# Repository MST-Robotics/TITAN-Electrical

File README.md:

# TITAN-Electrical

This repository holds the electrical schematics and board layouts for
the ROV (TITAN II) being built by the Missouri University of Science and
Technology Underwater Robotics Design Team.

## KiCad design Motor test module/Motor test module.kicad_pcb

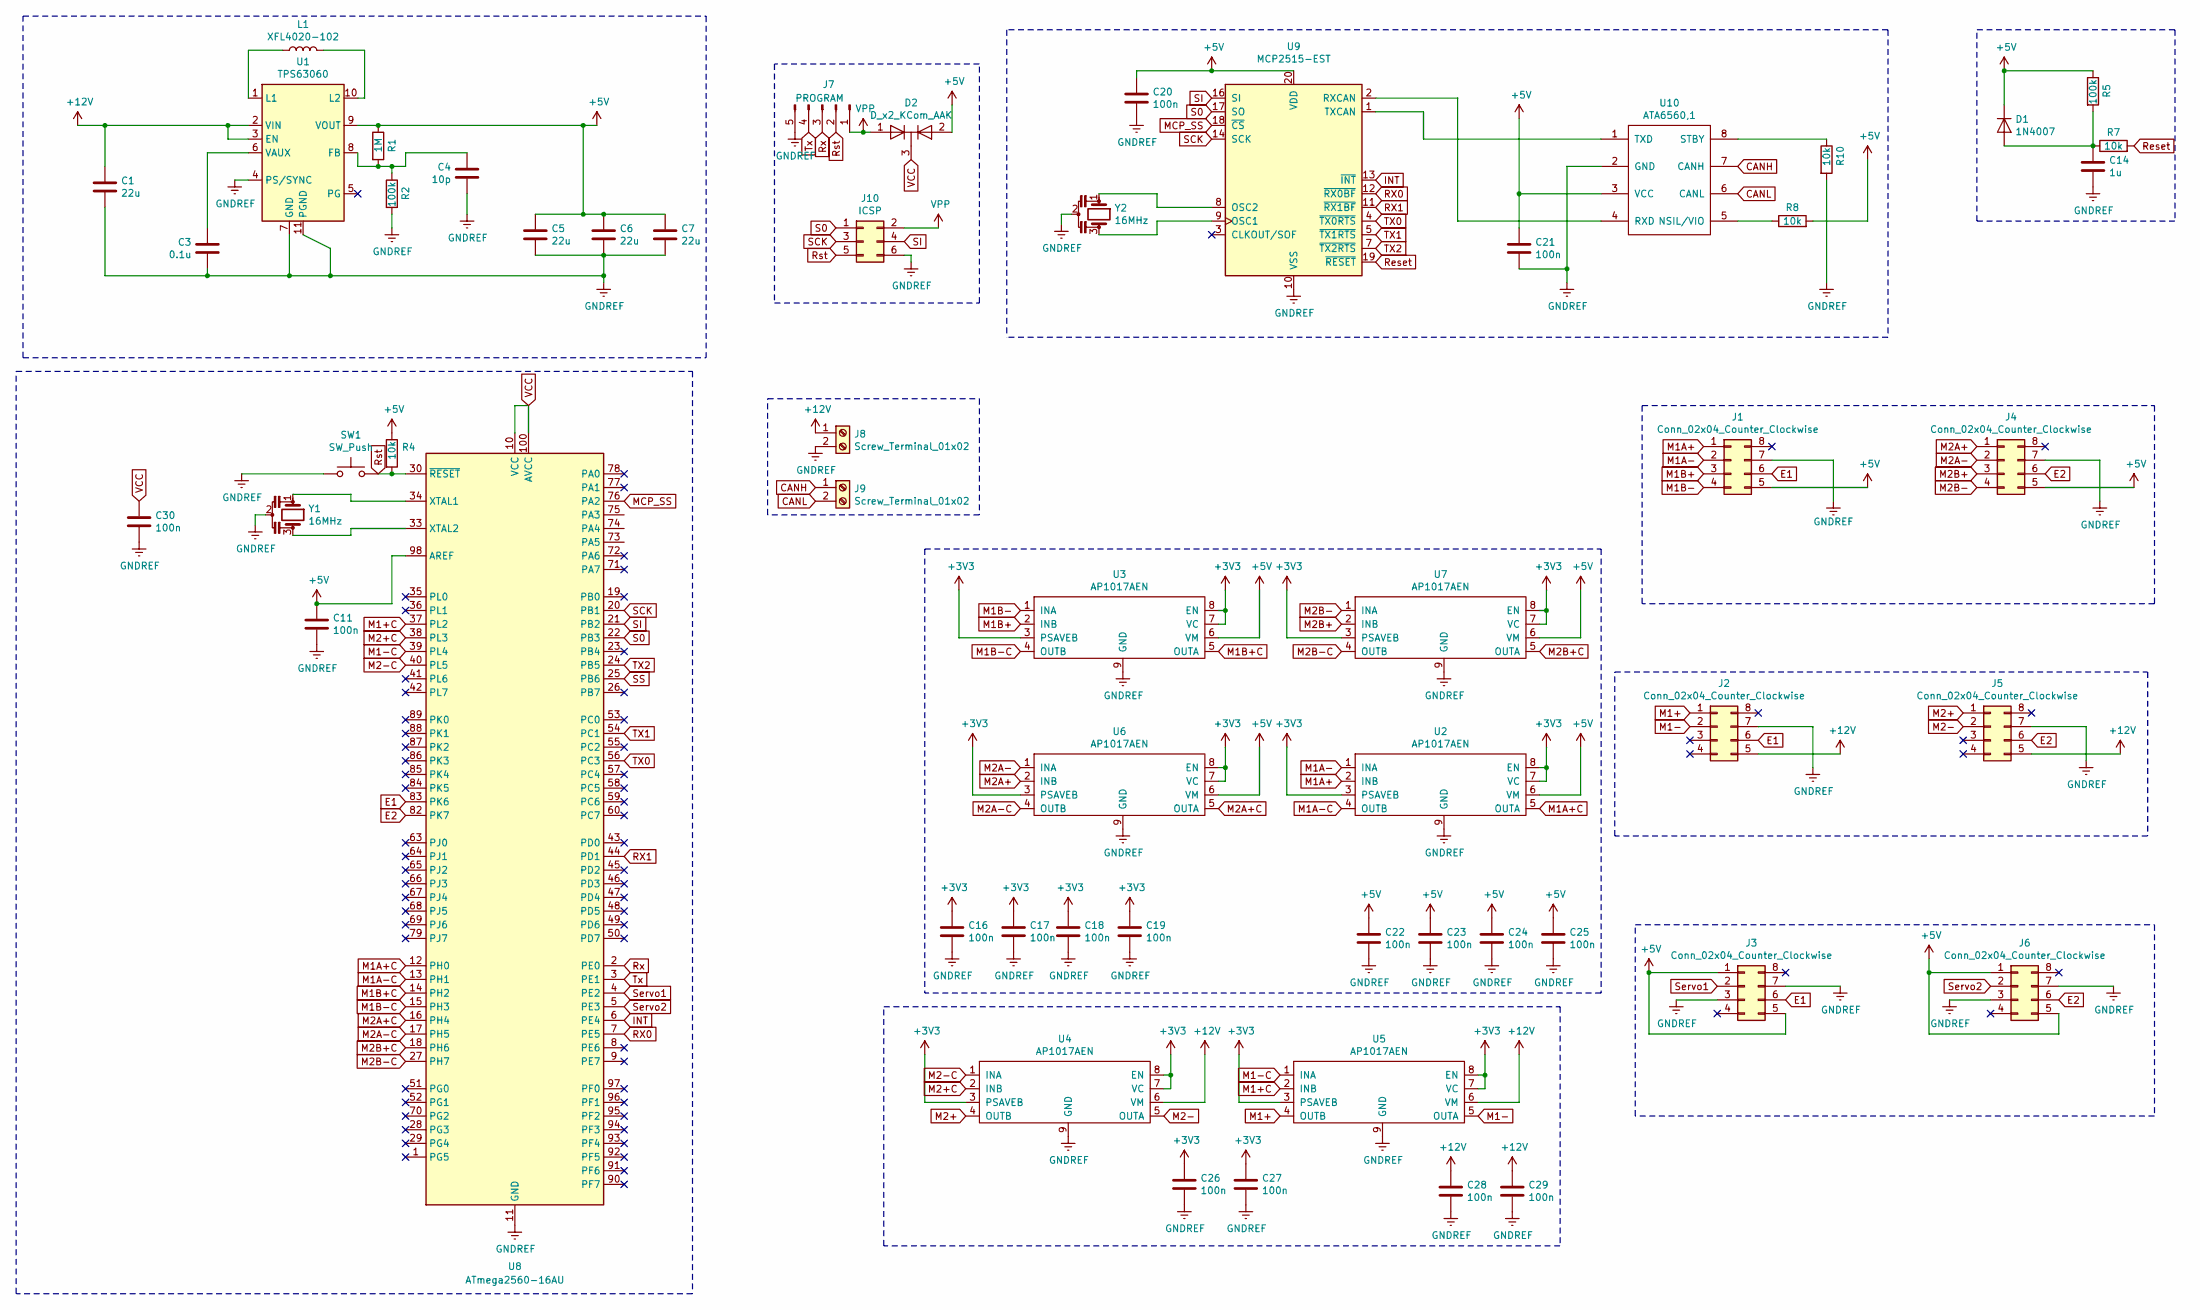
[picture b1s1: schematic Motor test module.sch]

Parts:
C1, C5, C6, C7: 22u; C_0805_2012Metric
C3: 0.1u; C_0603_1608Metric
C4: 10p; C_0603_1608Metric
C11, C16, C17, C18, C19, C20, C21, C22, C23, C24, C25, C26, C27, C28, C29, C30: 100n; C_0603_1608Metric
C14: 1u; C_0603_1608Metric
D1: 1N4007; D_DO-41_SOD81_P2.54mm_Vertical_AnodeUp
D2: D_x2_KCom_AAK; SOT-23
J1, J2, J3, J4, J5, J6: Conn_02x04_Counter_Clockwise; PinHeader_2x04_P2.54mm_Vertical
J7: PROGRAM; PinHeader_1x05_P2.54mm_Vertical
J8, J9: Screw_Terminal_01x02; TerminalBlock_bornier-2_P5.08mm
J10: ICSP; PinHeader_2x03_P2.54mm_Vertical
L1: XFL4020-102; L_0603_1608Metric
R1: 1M; R_0603_1608Metric
R2, R5: 100k; R_0603_1608Metric
R4, R7, R8, R10: 10k; R_0603_1608Metric
SW1: SW_Push; SW_PUSH_6mm
U1: TPS63060; Texas_S-PWSON-N10_ThermalVias
U2, U3, U4, U5, U6, U7: AP1017AEN; WSON-8-1EP_2x2mm_P0.5mm_EP0.9x1.6mm
U8: ATmega2560-16AU; TQFP-100_14x14mm_P0.5mm
U9: MCP2515-EST; TSSOP-20_4.4x6.5mm_P0.65mm
U10: ATA6560,1; SO-8_5.3x6.2mm_P1.27mm
Y1, Y2: 16MHz; Resonator_SMD_muRata_CSTxExxV-3Pin_3.0x1.1mm

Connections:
+3V3: C16.1, C17.1, C18.1, C19.1, C26.1, C27.1, U2.3 (PSAVEB), U2.7 (VC), U2.8 (EN), U3.3 (PSAVEB), U3.7 (VC), U3.8 (EN), U4.3 (PSAVEB), U4.7 (VC), U4.8 (EN), U5.3 (PSAVEB), U5.7 (VC), U5.8 (EN), U6.3 (PSAVEB), U6.7 (VC), U6.8 (EN), U7.3 (PSAVEB), U7.7 (VC), U7.8 (EN)
+5V: C5.1, C6.1, C7.1, C11.1, C20.1, C21.1, C22.1, C23.1, C24.1, C25.1, D1.1 (K), D2.2 (A), J1.5, J3.1, J3.5, J4.5, J6.1, J6.5, R1.1, R4.1, R5.1, R8.2, U1.9 (VOUT), U2.6 (VM), U3.6 (VM), U6.6 (VM), U7.6 (VM), U8.98 (AREF), U9.20 (VDD), U10.3 (VCC)
+12V: C1.1, C28.1, C29.1, J2.5, J5.5, J8.1, U1.2 (VIN), U1.3 (EN), U4.6 (VM), U5.6 (VM)
CANH: J9.1, U10.7 (CANH)
CANL: J9.2, U10.6 (CANL)
E1: J1.6, J2.6, J3.6, U8.83 (PK6)
E2: J4.6, J5.6, J6.6, U8.82 (PK7)
GNDREF: C1.2, C3.1, C4.1, C5.2, C6.2, C7.2, C11.2, C14.2, C16.2, C17.2, C18.2, C19.2, C20.2, C21.2, C22.2, C23.2, C24.2, C25.2, C26.2, C27.2, C28.2, C29.2, C30.2, J1.7, J2.7, J3.3, J3.7, J4.7, J5.7, J6.3, J6.7, J7.5, J8.2, J10.6, R2.2, R10.2, SW1.1, U1.4 (PS/SYNC), U1.7 (GND), U1.11 (PGND), U2.9 (GND), U3.9 (GND), U4.9 (GND), U5.9 (GND), U6.9 (GND), U7.9 (GND), U8.11 (GND), U8.32 (GND), U8.62 (GND), U8.81 (GND), U8.99 (GND), U9.10 (VSS), U10.2 (GND), Y1.2, Y2.2
INT: U8.6 (PE4), U9.13 (~INT)
M1+: J2.1, U5.4 (OUTB)
M1+C: U5.2 (INB), U8.37 (PL2)
M1-: J2.2, U5.5 (OUTA)
M1-C: U5.1 (INA), U8.39 (PL4)
M1A+: J1.1, U2.2 (INB)
M1A+C: U2.5 (OUTA), U8.12 (PH0)
M1A-: J1.2, U2.1 (INA)
M1A-C: U2.4 (OUTB), U8.13 (PH1)
M1B+: J1.3, U3.2 (INB)
M1B+C: U3.5 (OUTA), U8.14 (PH2)
M1B-: J1.4, U3.1 (INA)
M1B-C: U3.4 (OUTB), U8.15 (PH3)
M2+: J5.1, U4.4 (OUTB)
M2+C: U4.2 (INB), U8.38 (PL3)
M2-: J5.2, U4.5 (OUTA)
M2-C: U4.1 (INA), U8.40 (PL5)
M2A+: J4.1, U6.2 (INB)
M2A+C: U6.5 (OUTA), U8.16 (PH4)
M2A-: J4.2, U6.1 (INA)
M2A-C: U6.4 (OUTB), U8.17 (PH5)
M2B+: J4.3, U7.2 (INB)
M2B+C: U7.5 (OUTA), U8.18 (PH6)
M2B-: J4.4, U7.1 (INA)
M2B-C: U7.4 (OUTB), U8.27 (PH7)
MCP_SS: U8.76 (PA2), U9.18 (~CS)
unnamed: C3.2, U1.6 (VAUX)
unnamed: C4.2, R1.2, R2.1, U1.8 (FB)
unnamed: C14.1, D1.2 (A), R5.2, R7.1
unnamed: L1.1, U1.1 (L1)
unnamed: L1.2, U1.10 (L2)
unnamed: R8.1, U10.5 (NSIL/VIO)
unnamed: R10.1, U10.8 (STBY)
unnamed: U8.33 (XTAL2), Y1.3
unnamed: U8.34 (XTAL1), Y1.1
unnamed: U9.8 (OSC2), Y2.1
unnamed: U9.9 (OSC1), Y2.3
unnamed: U9.1 (TXCAN), U10.1 (TXD)
unnamed: U9.2 (RXCAN), U10.4 (RXD)
RX0: U8.7 (PE5), U9.12 (~RX0BF)
RX1: U8.44 (PD1), U9.11 (~RX1BF)
Reset: R7.2, U9.19 (~RESET)
Rst: J7.2, J10.5, R4.2, SW1.2, U8.30 (~RESET)
Rx: J7.3, U8.2 (PE0)
S0: J10.1, U8.22 (PB3), U9.17 (SO)
SCK: J10.3, U8.20 (PB1), U9.14 (SCK)
SI: J10.4, U8.21 (PB2), U9.16 (SI)
Servo1: J3.2, U8.4 (PE2)
Servo2: J6.2, U8.5 (PE3)
TX0: U8.56 (PC3), U9.4 (~TX0RTS)
TX1: U8.54 (PC1), U9.5 (~TX1RTS)
TX2: U8.24 (PB5), U9.7 (~TX2RTS)
Tx: J7.4, U8.3 (PE1)
VCC: C30.1, D2.3 (K), U8.10 (VCC), U8.31 (VCC), U8.61 (VCC), U8.80 (VCC), U8.100 (AVCC)
VPP: D2.1 (A), J7.1, J10.2

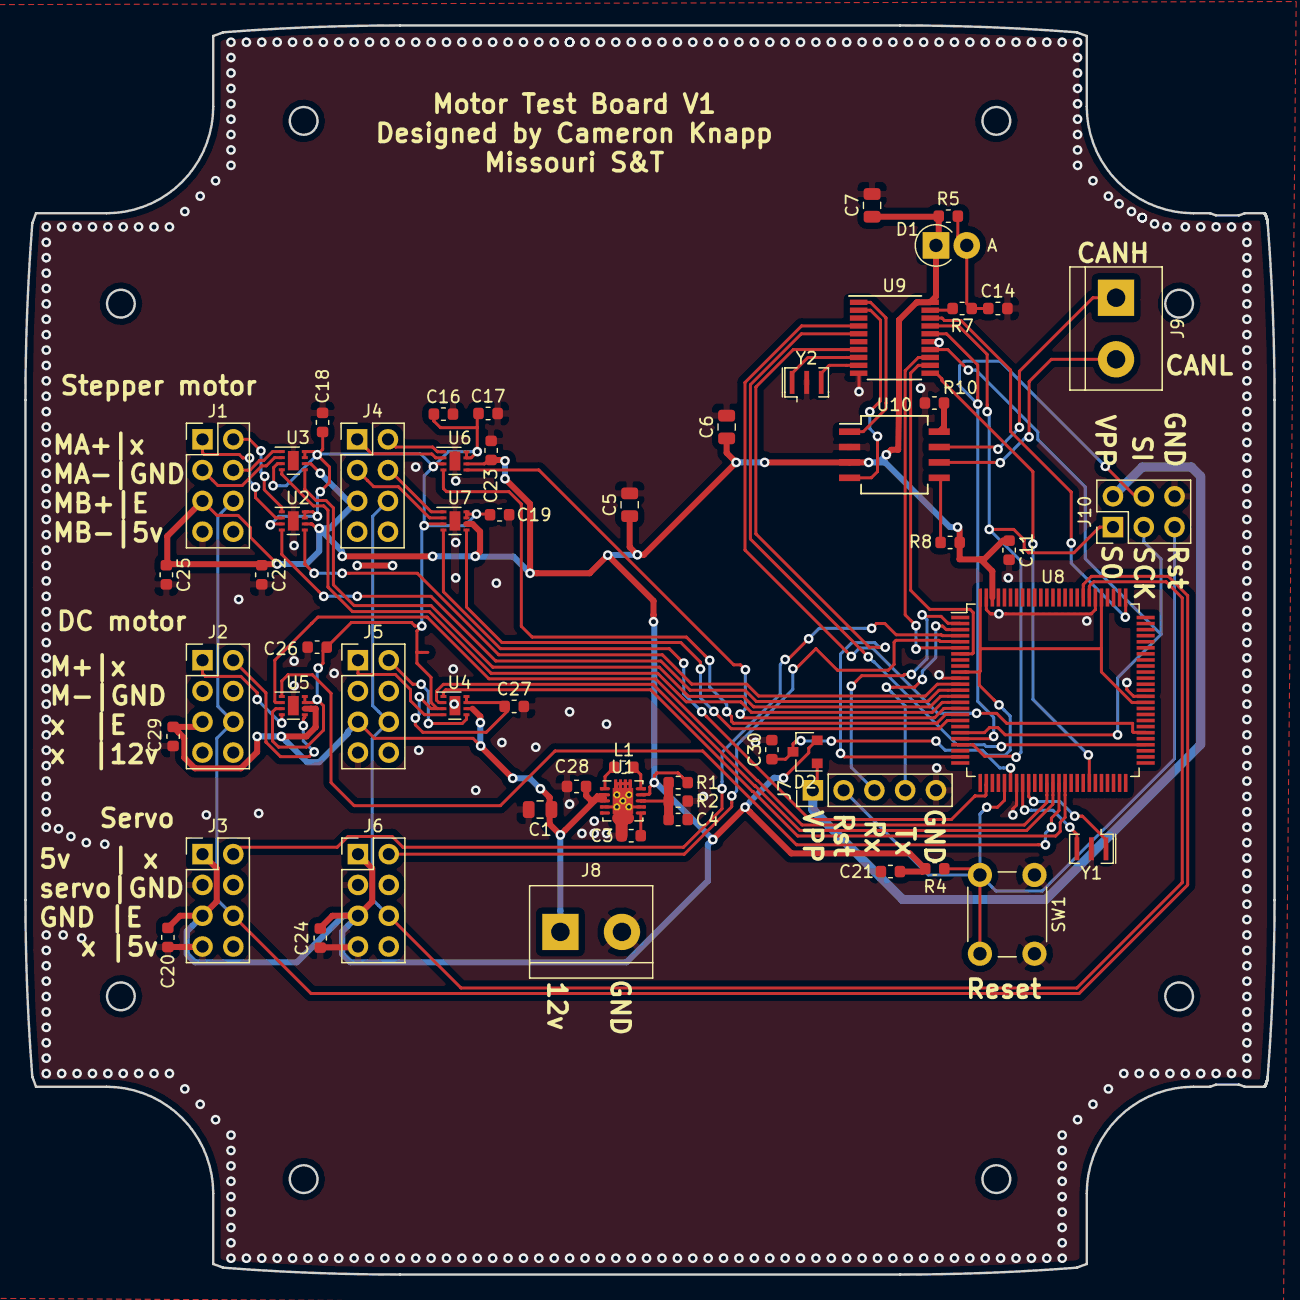
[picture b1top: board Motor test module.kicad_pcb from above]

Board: 2 copper layers, 103.1 x 103.1 mm, 56 parts (0 on the bottom side), 63 nets.

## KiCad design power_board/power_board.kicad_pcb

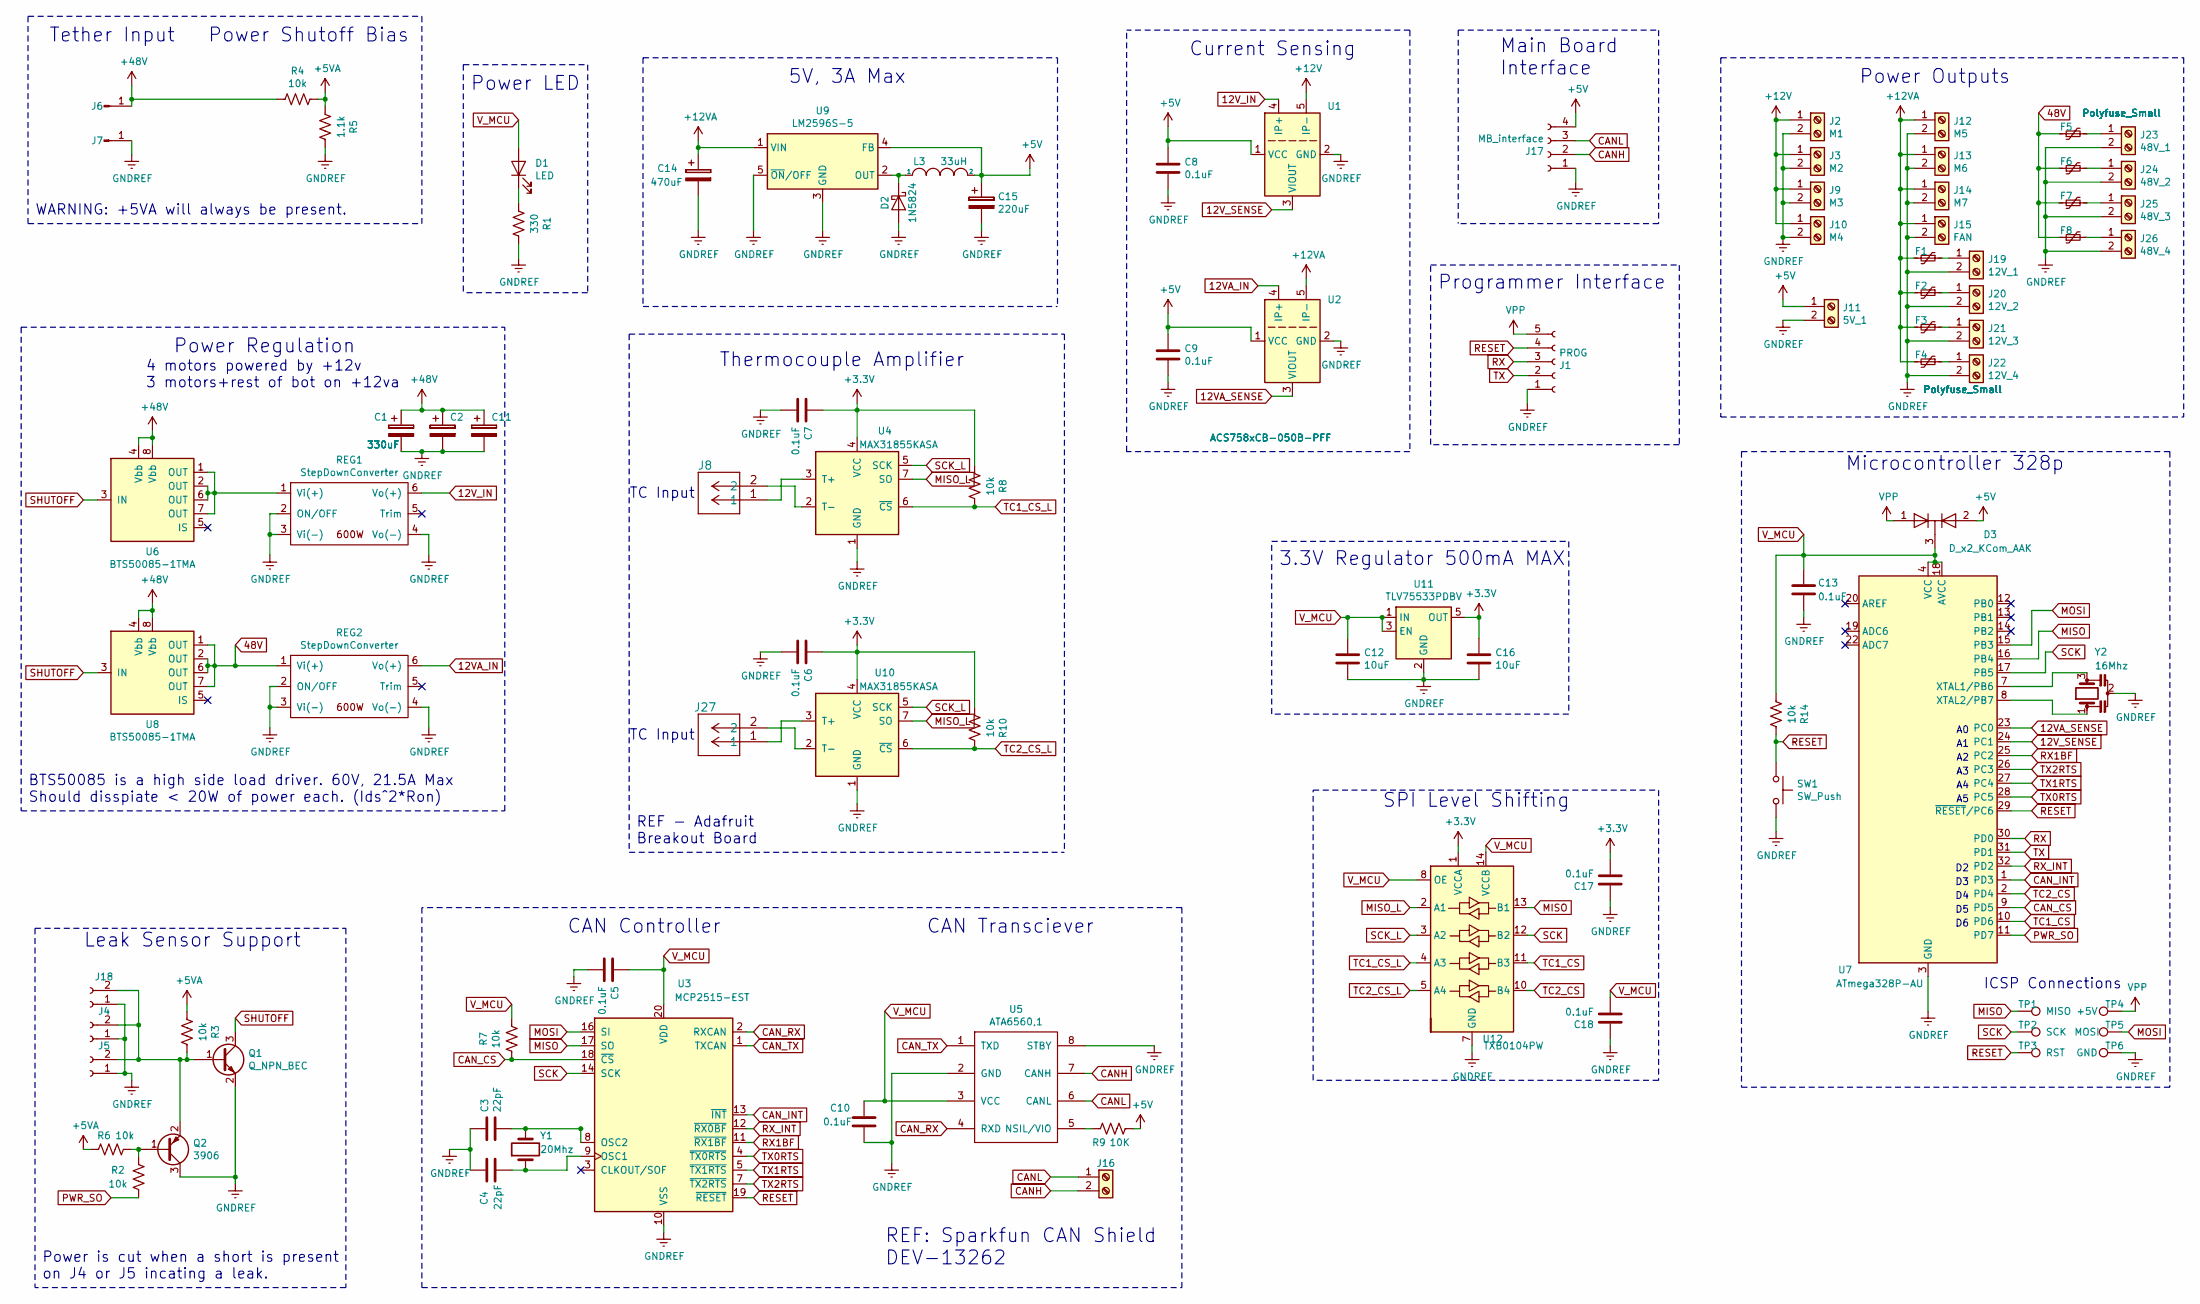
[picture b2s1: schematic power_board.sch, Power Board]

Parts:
C1, C2, C11: 330uF; CP_Radial_D10.0mm_P5.00mm
C3, C4: 22pF; C_0603_1608Metric
C5, C6, C7, C8, C9, C10, C13, C17, C18: 0.1uF; C_0603_1608Metric
C12, C16: 10uF; C_0805_2012Metric
C14: 470uF; CP_Radial_D8.0mm_P5.00mm
C15: 220uF; CP_Radial_D5.0mm_P2.50mm
D1: LED; LED_0603_1608Metric
D2: 1N5824; D_SMC
D3: D_x2_KCom_AAK; SOT-23
F1, F2, F3, F4, F5, F6, F7, F8: Polyfuse_Small; Fuse_2920_7451Metric
J1: PROG; PinHeader_1x05_P2.54mm_Vertical
J2: M1; TerminalBlock_bornier-2_P5.08mm
J3: M2; TerminalBlock_bornier-2_P5.08mm
J4, J5, J18: Conn_01x02_Female; JST_GH_BM02B-GHS-TBT_1x02-1MP_P1.25mm_Vertical
J6, J7: Conn_01x01_Male; Banana_Jack_1Pin
J8, J27: 282834-2
J9: M3; TerminalBlock_bornier-2_P5.08mm
J10: M4; TerminalBlock_bornier-2_P5.08mm
J11: 5V_1; TerminalBlock_bornier-2_P5.08mm
J12: M5; TerminalBlock_bornier-2_P5.08mm
J13: M6; TerminalBlock_bornier-2_P5.08mm
J14: M7; TerminalBlock_bornier-2_P5.08mm
J15: FAN; TerminalBlock_bornier-2_P5.08mm
J16: Screw_Terminal_01x02; TerminalBlock_bornier-2_P5.08mm
J17: MB_interface; PinHeader_1x04_P2.54mm_Vertical
J19: 12V_1; TerminalBlock_bornier-2_P5.08mm
J20: 12V_2; TerminalBlock_bornier-2_P5.08mm
J21: 12V_3; TerminalBlock_bornier-2_P5.08mm
J22: 12V_4; TerminalBlock_bornier-2_P5.08mm
J23: 48V_1; TerminalBlock_bornier-2_P5.08mm
J24: 48V_2; TerminalBlock_bornier-2_P5.08mm
J25: 48V_3; TerminalBlock_bornier-2_P5.08mm
J26: 48V_4; TerminalBlock_bornier-2_P5.08mm
L3: 33uH; L_Bourns_SRP1245A
Q1: Q_NPN_BEC; SOT-23
Q2: 3906; SOT-23
R1: 330; R_0603_1608Metric
R2, R3, R4, R6, R7, R8, R10, R14: 10k; R_0603_1608Metric
R5: 1.1k; R_0603_1608Metric
R9: 10K; R_0603_1608Metric
REG1, REG2: StepDownConverter; Q54SG
SW1: SW_Push; SW_PUSH_6mm
TP1: MISO; TestPoint_Pad_D1.0mm
TP2: SCK; TestPoint_Pad_D1.0mm
TP3: RST; TestPoint_Pad_D1.0mm
TP4: +5V; TestPoint_Pad_D1.0mm
TP5: MOSI; TestPoint_Pad_D1.0mm
TP6: GND; TestPoint_Pad_D1.0mm
U1, U2: ACS758xCB-050B-PFF; Allegro_CB_PFF
U3: MCP2515-EST; TSSOP-20_4.4x6.5mm_P0.65mm
U4, U10: MAX31855KASA; SOIC-8_3.9x4.9mm_P1.27mm
U5: ATA6560,1; SOIC-8_3.9x4.9mm_P1.27mm
U6, U8: BTS50085-1TMA; Infineon_PG-TO-220-7Lead_TabPin8
U7: ATmega328P-AU; TQFP-32_7x7mm_P0.8mm
U9: LM2596S-5; TO-263-5_TabPin3
U11: TLV75533PDBV; SOT-23-5
U12: TXB0104PW; TSSOP-14_4.4x5mm_P0.65mm
Y1: 20Mhz; Crystal_SMD_0603-2Pin_6.0x3.5mm
Y2: 16Mhz; OSC_CSTCE16M0V53-R0

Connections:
12VA_IN: REG2.6 (Vo(+)), U2.4 (IP+)
12VA_SENSE: U2.3 (VIOUT), U7.23 (PC0)
12V_IN: REG1.6 (Vo(+)), U1.4 (IP+)
12V_SENSE: U1.3 (VIOUT), U7.24 (PC1)
48V: F5.1, F6.1, F7.1, F8.1, REG2.1 (Vi(+)), U8.1 (OUT), U8.2 (OUT), U8.6 (OUT), U8.7 (OUT)
+3V3: C6.1, C7.1, C16.1, C17.2, R8.1, R10.1, U4.4 (VCC), U10.4 (VCC), U11.5 (OUT), U12.1 (VCCA)
+5V: C8.1, C9.1, C15.1, D3.2 (A), J11.1, J17.4, L3.2, R9.2, U1.1 (VCC), U2.1 (VCC), U9.4 (FB)
+5VA: R3.2, R4.1, R5.2, R6.2
+12V: J2.1, J3.1, J9.1, J10.1, U1.5 (IP-)
+12VA: C14.1, F1.2, F2.2, F3.2, F4.2, J12.1, J13.1, J14.1, J15.1, U2.5 (IP-), U9.1 (VIN)
+48V: C1.1, C2.1, C11.1, J6.1, R4.2, U6.4 (Vbb), U6.8 (Vbb), U8.4 (Vbb), U8.8 (Vbb)
CANH: J16.2, J17.2, U5.7 (CANH)
CANL: J16.1, J17.3, U5.6 (CANL)
CAN_CS: R7.1, U3.18 (~CS), U7.9 (PD5)
CAN_INT: U3.13 (~INT), U7.1 (PD3)
CAN_RX: U3.2 (RXCAN), U5.4 (RXD)
CAN_TX: U3.1 (TXCAN), U5.1 (TXD)
GNDREF: C1.2, C2.2, C3.1, C4.2, C5.2, C6.2, C7.2, C8.2, C9.2, C10.2, C11.2, C12.2, C13.2, C14.2, C15.2, C16.2, C17.1, C18.1, D2.2 (A), J1.1, J2.2, J3.2, J4.1, J5.1, J7.1, J9.2, J10.2, J11.2, J12.2, J13.2, J14.2, J15.2, J17.1, J18.1, J19.2, J20.2, J21.2, J22.2, J23.2, J24.2, J25.2, J26.2, Q1.2 (E), Q2.3 (C), R1.2, R5.1, REG1.2 (ON/OFF), REG1.3 (Vi(-)), REG1.4 (Vo(-)), REG2.2 (ON/OFF), REG2.3 (Vi(-)), REG2.4 (Vo(-)), SW1.2, TP6.1, U1.2 (GND), U2.2 (GND), U3.10 (VSS), U4.1 (GND), U5.2 (GND), U5.8 (STBY), U7.3 (GND), U7.5 (GND), U7.21 (GND), U9.3 (GND), U9.5 (~ON~/OFF), U10.1 (GND), U11.2 (GND), U12.7 (GND), Y2.2
MISO: TP1.1, U3.17 (SO), U7.16 (PB4), U12.13 (B1)
MISO_L: U4.7 (SO), U10.7 (SO), U12.2 (A1)
MOSI: TP5.1, U3.16 (SI), U7.15 (PB3)
unnamed: C3.2, U3.8 (OSC2), U3.15 (NC), Y1.2
unnamed: C4.1, U3.9 (OSC1), Y1.1
unnamed: D1.1 (K), R1.1
unnamed: D2.1 (K), L3.1, U9.2 (OUT)
unnamed: F1.1, J19.1
unnamed: F2.1, J20.1
unnamed: F3.1, J21.1
unnamed: F4.1, J22.1
unnamed: F5.2, J23.1
unnamed: F6.2, J24.1
unnamed: F7.2, J25.1
unnamed: F8.2, J26.1
unnamed: J8.1, U4.3 (T+)
unnamed: J8.2, U4.2 (T-)
unnamed: J4.2, J5.2, J18.2, Q1.1 (B), Q2.2 (E), R3.1
unnamed: J27.1, U10.3 (T+)
unnamed: J27.2, U10.2 (T-)
unnamed: Q2.1 (B), R2.1, R6.1
unnamed: R9.1, U5.5 (NSIL/VIO)
unnamed: REG1.1 (Vi(+)), U6.1 (OUT), U6.2 (OUT), U6.6 (OUT), U6.7 (OUT)
unnamed: U7.7 (XTAL1/PB6), Y2.3
unnamed: U7.8 (XTAL2/PB7), Y2.1
PWR_SO: R2.2, U7.11 (PD7)
RESET: J1.4, R14.2, SW1.1, TP3.1, U3.19 (~RESET), U7.29 (~RESET~/PC6)
RX: J1.3, U7.30 (PD0)
RX1BF: U3.11 (~RX1BF), U7.25 (PC2)
RX_INT: U3.12 (~RX0BF), U7.32 (PD2)
SCK: TP2.1, U3.14 (SCK), U7.17 (PB5), U12.12 (B2)
SCK_L: U4.5 (SCK), U10.5 (SCK), U12.3 (A2)
SHUTOFF: Q1.3 (C), U6.3 (IN), U8.3 (IN)
TC1_CS: U7.10 (PD6), U12.11 (B3)
TC1_CS_L: R8.2, U4.6 (~CS~), U12.4 (A3)
TC2_CS: U7.2 (PD4), U12.10 (B4)
TC2_CS_L: R10.2, U10.6 (~CS~), U12.5 (A4)
TX: J1.2, U7.31 (PD1)
TX0RTS: U3.4 (~TX0RTS), U7.28 (PC5)
TX1RTS: U3.5 (~TX1RTS), U7.27 (PC4)
TX2RTS: U3.7 (~TX2RTS), U7.26 (PC3)
VPP: D3.1 (A), J1.5, TP4.1
V_MCU: C5.1, C10.1, C12.1, C13.1, C18.2, D1.2 (A), D3.3 (K), R7.2, R14.1, U3.20 (VDD), U5.3 (VCC), U7.4 (VCC), U7.6 (VCC), U7.18 (AVCC), U11.1 (IN), U11.3 (EN), U12.8 (OE), U12.14 (VCCB)

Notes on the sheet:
5V, 3A Max
4 motors powered by +12v 3 motors+rest of bot on +12va
Leak Sensor Support
Tether Input
Power Outputs
Current Sensing
Microcontroller 328p
Thermocouple Amplifier
TC Input
REF - Adafruit Breakout Board
CAN Controller
CAN Transciever
REF: Sparkfun CAN Shield DEV-13262
Power LED
Programmer Interface
WARNING: +5VA will always be present.
Power Regulation
Power Shutoff Bias
Power is cut when a short is present on J4 or J5 incating a leak.
BTS50085 is a high side load driver. 60V, 21.5A Max Should disspiate < 20W of power each. (Ids^2*Ron)
Main Board Interface
ICSP Connections
3.3V Regulator 500mA MAX
SPI Level Shifting

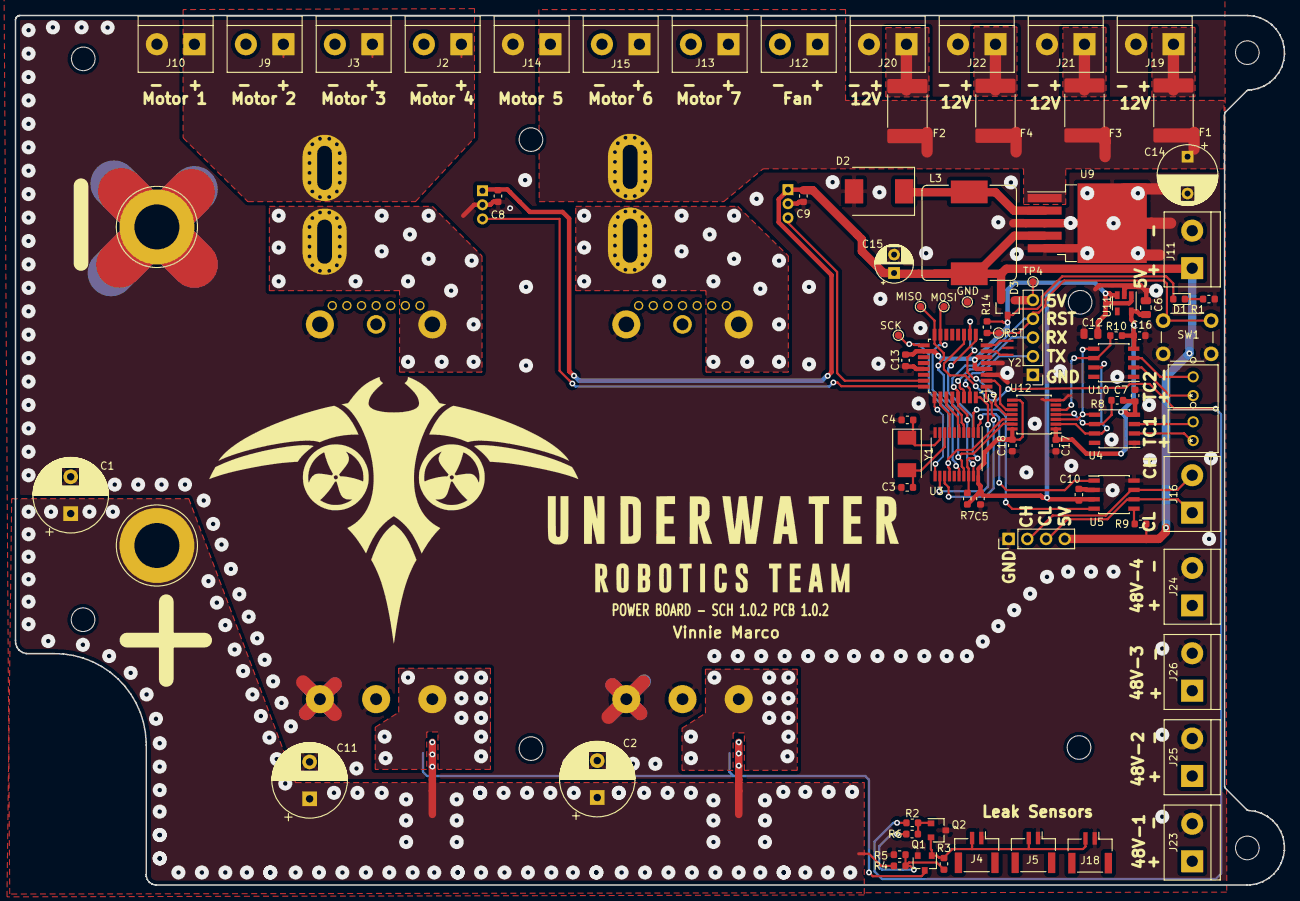
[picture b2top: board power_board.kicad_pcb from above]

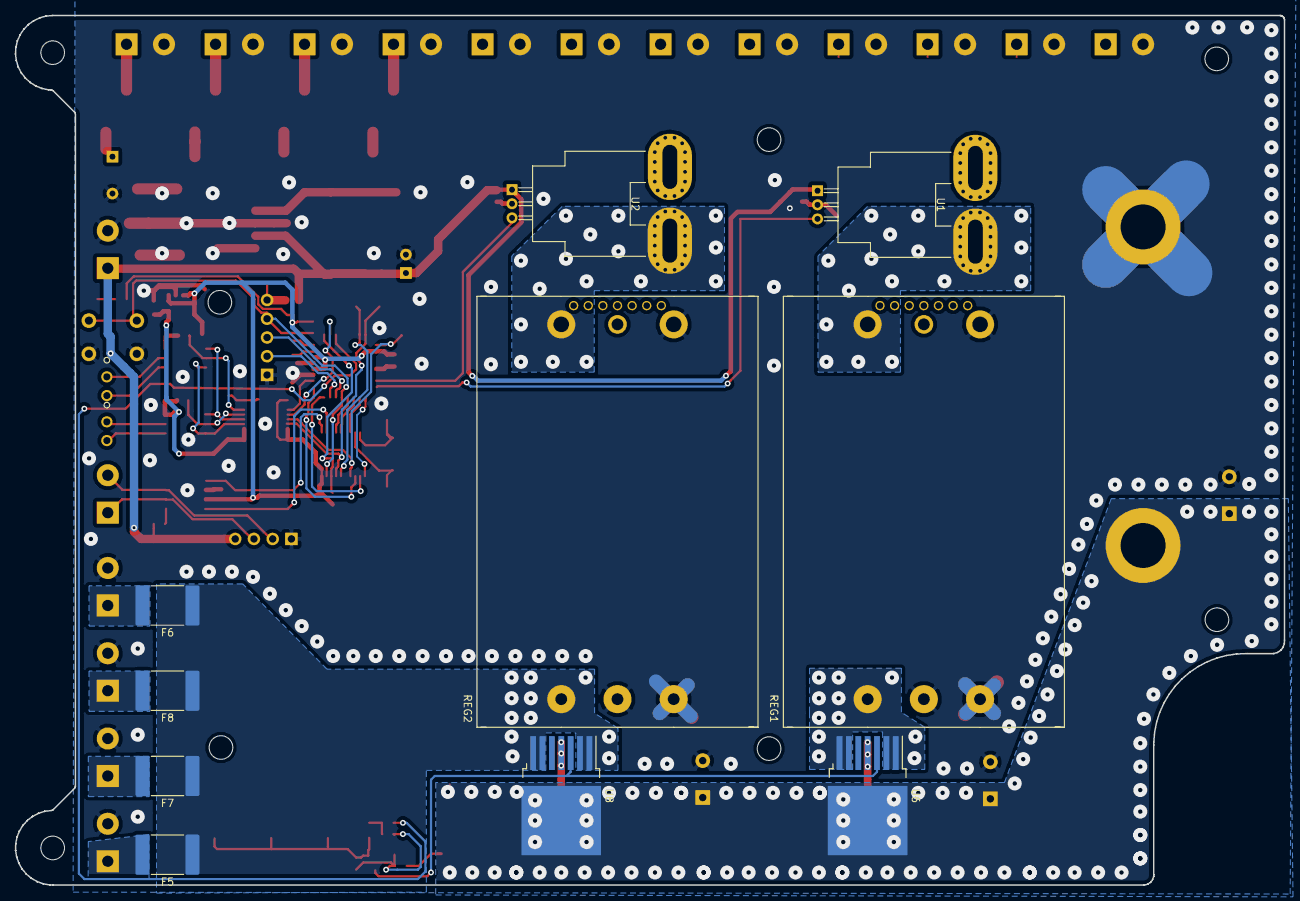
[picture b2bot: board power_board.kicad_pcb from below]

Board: 2 copper layers, 172.0 x 117.9 mm, 93 parts (10 on the bottom side), 61 nets.

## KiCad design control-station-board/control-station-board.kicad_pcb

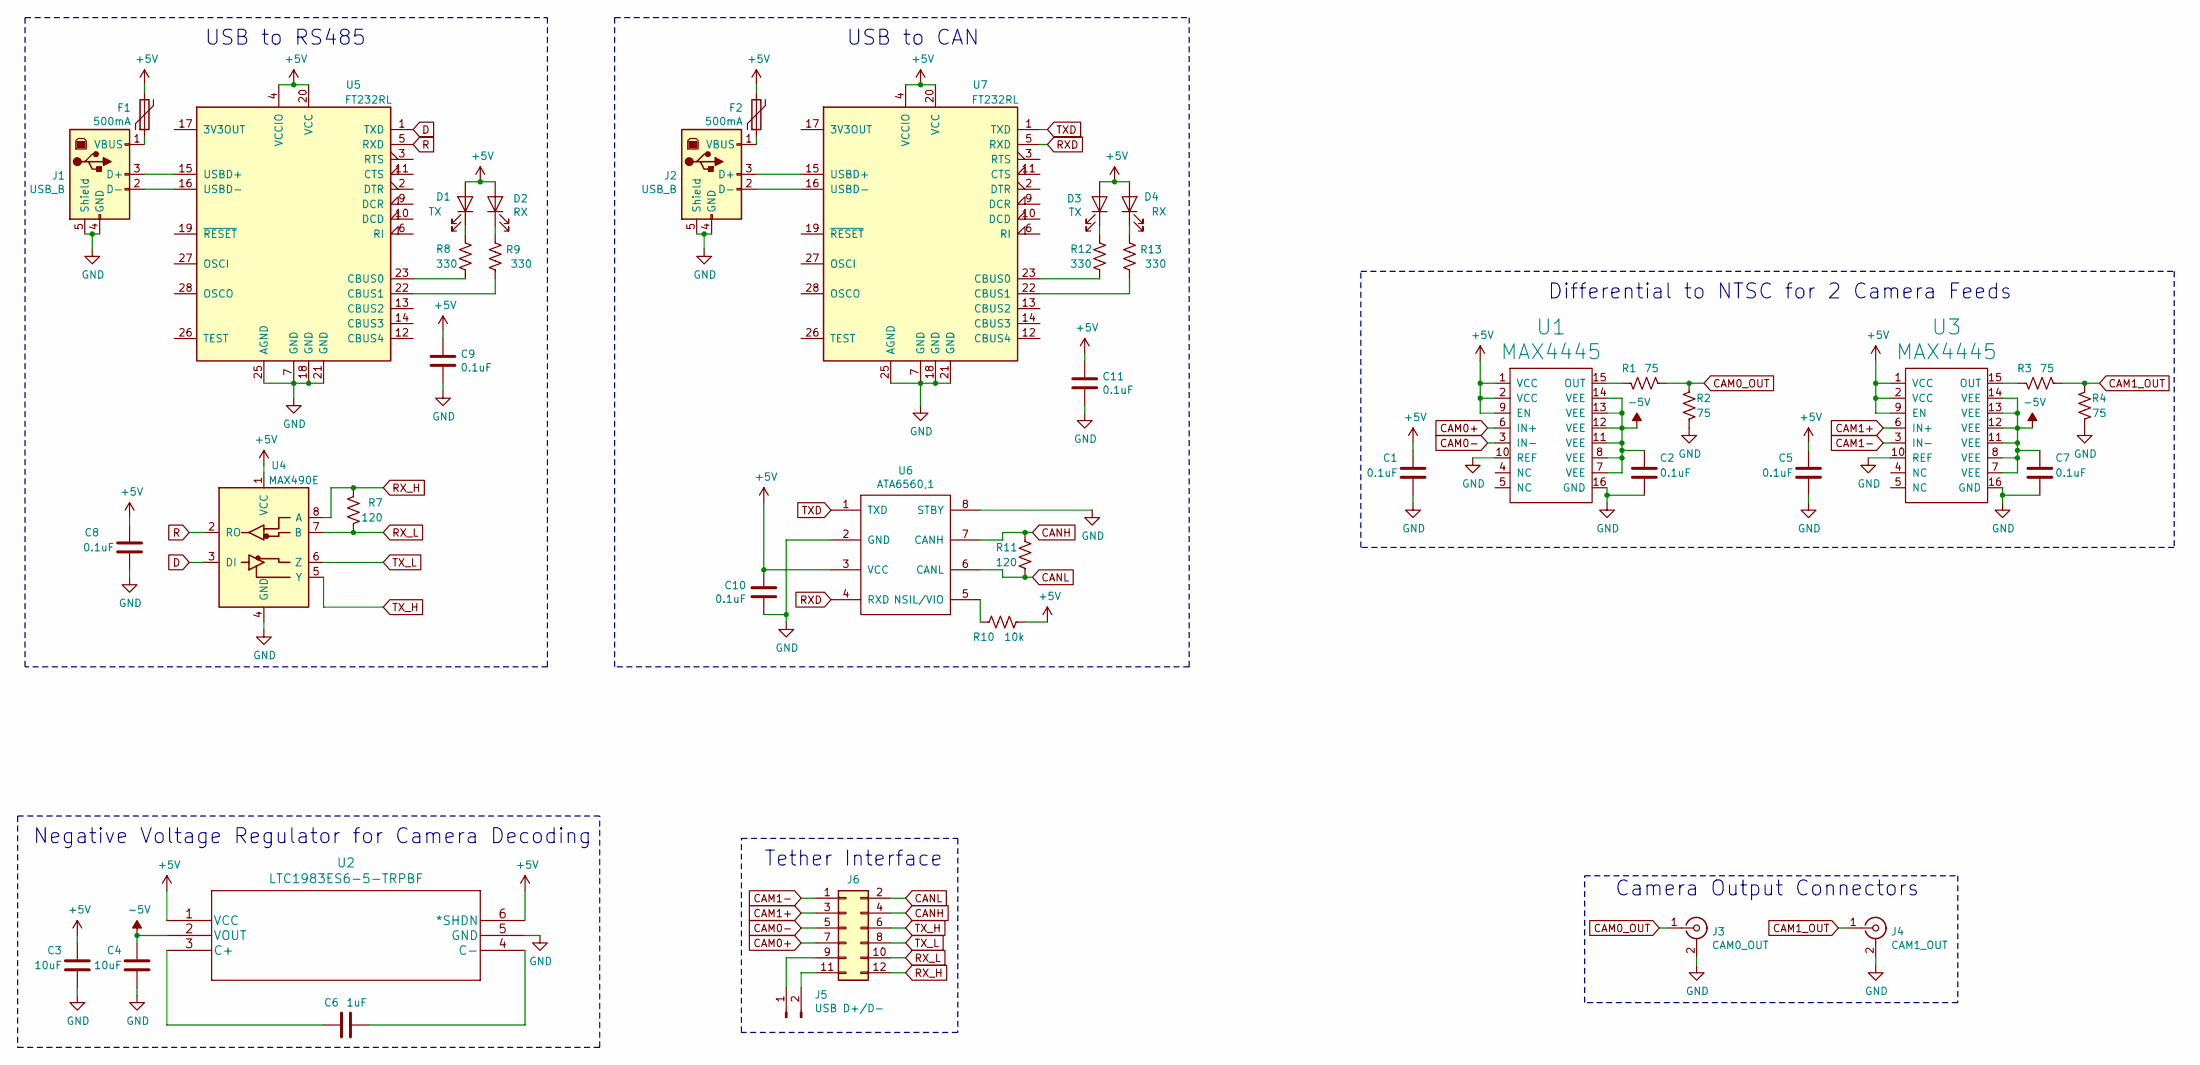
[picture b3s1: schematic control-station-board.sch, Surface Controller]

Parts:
C1, C2, C5, C7, C8, C9, C10, C11: 0.1uF; C_0603_1608Metric
C3, C4: 10uF; C_0805_2012Metric
C6: 1uF; C_0805_2012Metric
D1, D3: TX; LED_0603_1608Metric
D2, D4: RX; LED_0603_1608Metric
F1, F2: 500mA; Fuse_0805_2012Metric
J1, J2: USB_B; USB_B_TE_5787834_Vertical
J3: CAM0_OUT; CUI_RCJ-044
J4: CAM1_OUT; CUI_RCJ-044
J5: USB D+/D-; PinHeader_1x02_P2.54mm_Vertical
J6: Conn_02x06_Odd_Even; PinHeader_2x06_P2.54mm_Vertical
R1, R2, R3, R4: 75; R_0603_1608Metric
R7, R11: 120; R_0603_1608Metric
R8, R9, R12, R13: 330; R_0603_1608Metric
R10: 10k; R_0603_1608Metric
U1, U3: MAX4445; SOIC-16_3.9x9.9mm_P1.27mm
U2: LTC1983ES6-5-TRPBF; SOT-23-6
U4: MAX490E; SOIC-8_3.9x4.9mm_P1.27mm
U5, U7: FT232RL; SSOP-28_5.3x10.2mm_P0.65mm
U6: ATA6560,1; SOIC-8_3.9x4.9mm_P1.27mm

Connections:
+5V: C1.1, C3.1, C5.1, C8.2, C9.1, C10.1, C11.1, D1.2 (A), D2.2 (A), D3.2 (A), D4.2 (A), F1.2, F2.2, R10.2, U1.1 (VCC), U1.2 (VCC), U1.9 (EN), U2.1 (VCC), U2.6 (*SHDN), U3.1 (VCC), U3.2 (VCC), U3.9 (EN), U4.1 (VCC), U5.4 (VCCIO), U5.20 (VCC), U6.3 (VCC), U7.4 (VCCIO), U7.20 (VCC)
-5V: C2.1, C4.1, C7.1, U1.7 (VEE), U1.8 (VEE), U1.11 (VEE), U1.12 (VEE), U1.13 (VEE), U1.14 (VEE), U2.2 (VOUT), U3.7 (VEE), U3.8 (VEE), U3.11 (VEE), U3.12 (VEE), U3.13 (VEE), U3.14 (VEE)
CAM0+: J6.7, U1.6 (IN+)
CAM0-: J6.5, U1.3 (IN-)
CAM0_OUT: J3.1 (In), R1.2, R2.1
CAM1+: J6.3, U3.6 (IN+)
CAM1-: J6.1, U3.3 (IN-)
CAM1_OUT: J4.1 (In), R3.2, R4.1
CANH: J6.4, R11.1, U6.7 (CANH)
CANL: J6.2, R11.2, U6.6 (CANL)
D: U4.3 (DI), U5.1 (TXD)
GND: C1.2, C2.2, C3.2, C4.2, C5.2, C7.2, C8.1, C9.2, C10.2, C11.2, J1.4 (GND), J1.5 (Shield), J2.4 (GND), J2.5 (Shield), J3.2 (Ext), J4.2 (Ext), R2.2, R4.2, U1.10 (REF), U1.16 (GND), U2.5 (GND), U3.10 (REF), U3.16 (GND), U4.4 (GND), U5.7 (GND), U5.18 (GND), U5.21 (GND), U5.25 (AGND), U6.2 (GND), U6.8 (STBY), U7.7 (GND), U7.18 (GND), U7.21 (GND), U7.25 (AGND)
unnamed: C6.1, U2.4 (C-)
unnamed: C6.2, U2.3 (C+)
unnamed: D1.1 (K), R8.1
unnamed: D2.1 (K), R9.1
unnamed: D3.1 (K), R12.1
unnamed: D4.1 (K), R13.1
unnamed: F1.1, J1.1 (VBUS)
unnamed: F2.1, J2.1 (VBUS)
unnamed: J1.2 (D-), U5.16 (USBD-)
unnamed: J1.3 (D+), U5.15 (USBD+)
unnamed: J2.2 (D-), U7.16 (USBD-)
unnamed: J2.3 (D+), U7.15 (USBD+)
unnamed: J5.1, J6.9
unnamed: J5.2, J6.11
unnamed: R1.1, U1.15 (OUT)
unnamed: R3.1, U3.15 (OUT)
unnamed: R8.2, U5.23 (CBUS0)
unnamed: R9.2, U5.22 (CBUS1)
unnamed: R10.1, U6.5 (NSIL/VIO)
unnamed: R12.2, U7.23 (CBUS0)
unnamed: R13.2, U7.22 (CBUS1)
R: U4.2 (RO), U5.5 (RXD)
RXD: U6.4 (RXD), U7.5 (RXD)
RX_H: J6.12, R7.1, U4.8 (A)
RX_L: J6.10, R7.2, U4.7 (B)
TXD: U6.1 (TXD), U7.1 (TXD)
TX_H: J6.6, U4.5 (Y)
TX_L: J6.8, U4.6 (Z)

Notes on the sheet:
USB to RS485
USB to CAN
Differential to NTSC for 2 Camera Feeds
Negative Voltage Regulator for Camera Decoding
Camera Output Connectors
Tether Interface

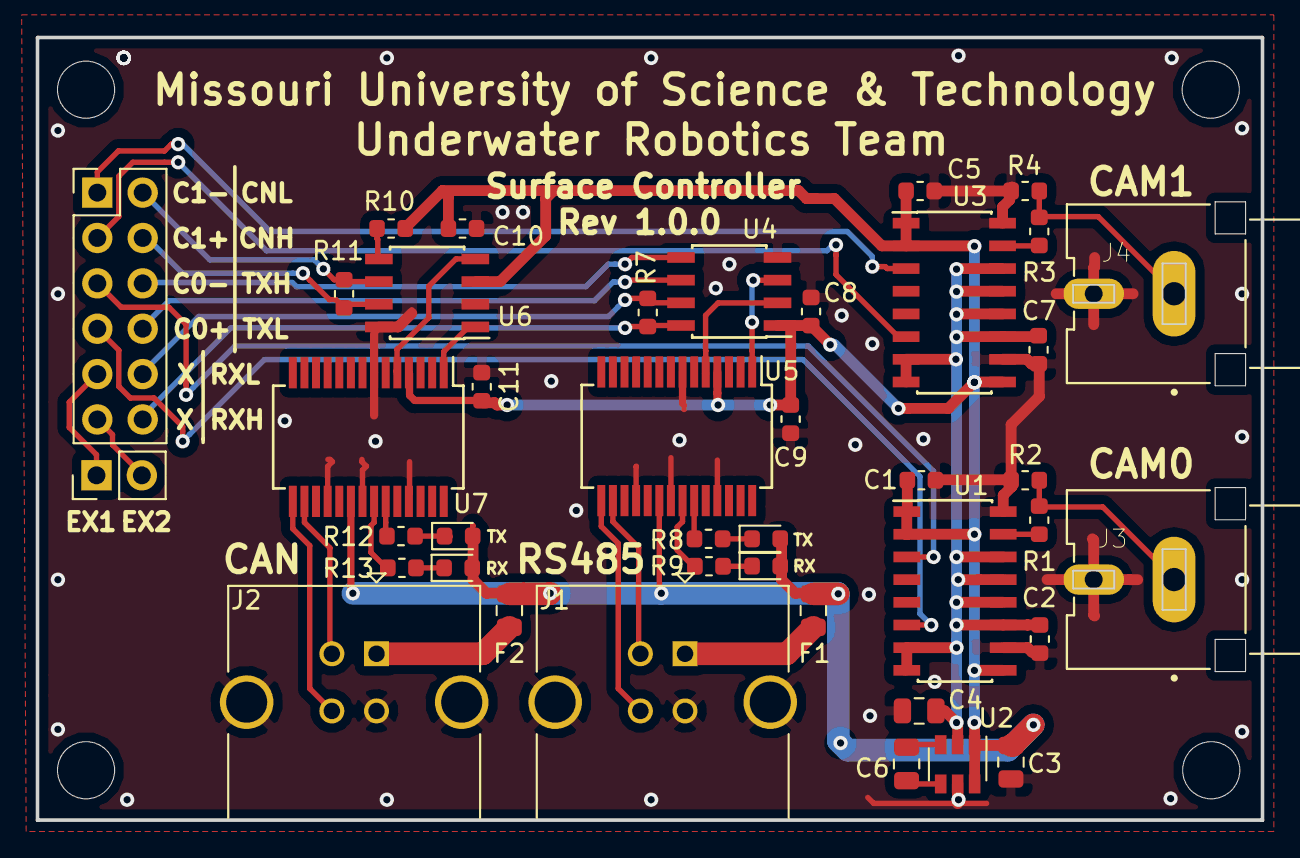
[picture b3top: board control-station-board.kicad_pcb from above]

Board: 2 copper layers, 68.6 x 43.8 mm, 41 parts (0 on the bottom side), 40 nets.

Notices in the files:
parts and their libraries:
Copyright 2016 Accelerated Designs. All rights reserved.
